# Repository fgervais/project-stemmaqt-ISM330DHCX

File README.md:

# ISM330DHCX Stemma QT Board

## Bus Pirate

### Read WHO_AM_I (Console)

```
HiZ> m
(1)> 4 (I2C)
(1)> 3 (~100KHz)

I2C> W
I2C> (1)
I2C> [0xd4 0x0f [0xd5 r]
I2C> w
```

## OSHPark

<a href="https://oshpark.com/shared_projects/3tg55XeU" target="_blank">https://oshpark.com/shared_projects/3tg55XeU</a>

## Related Projects

<a href="https://github.com/fgervais/project-nrf-princess-dress" target="_blank">https://github.com/fgervais/project-nrf-princess-dress</a>

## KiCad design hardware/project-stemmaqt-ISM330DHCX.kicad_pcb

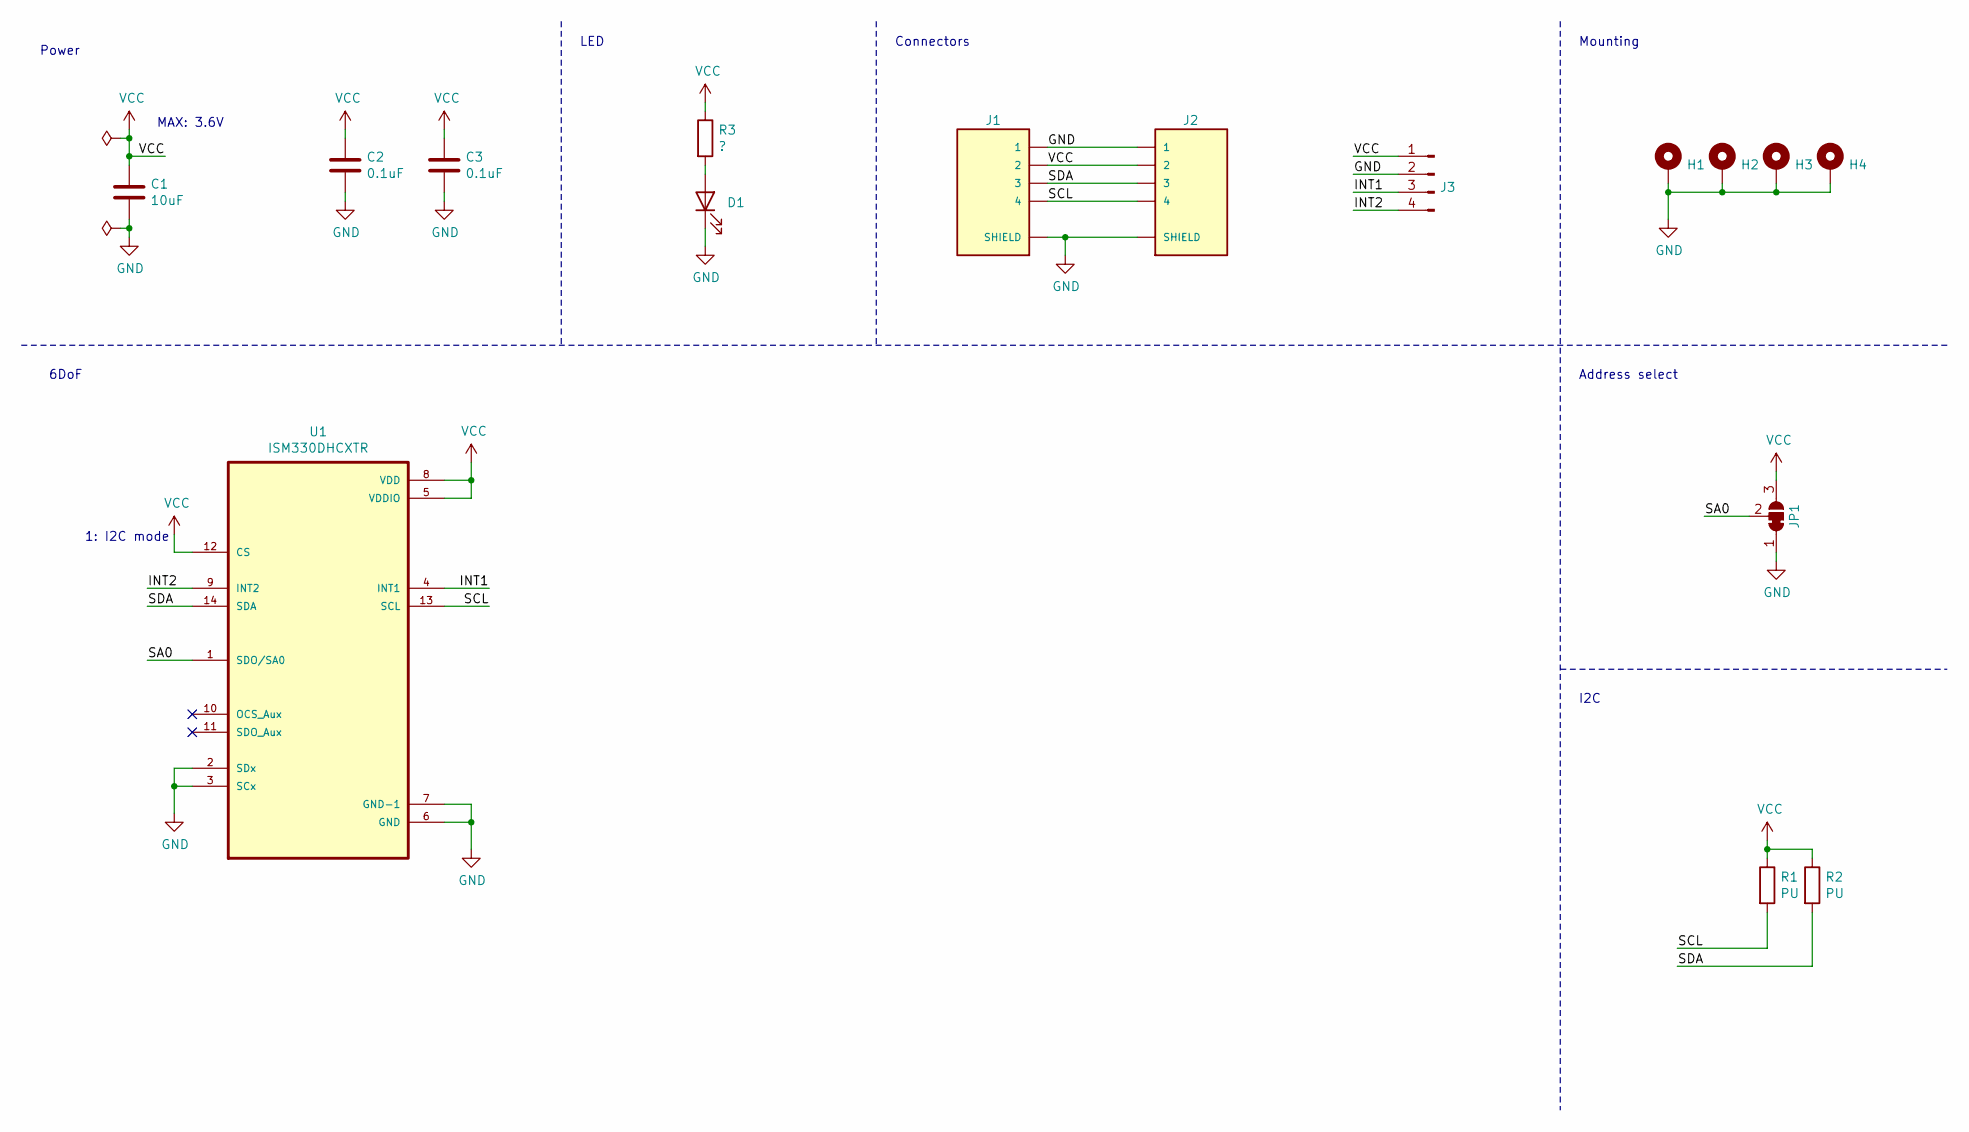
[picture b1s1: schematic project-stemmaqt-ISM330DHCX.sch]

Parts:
C1: 10uF; C_0805_2012Metric
C2, C3: 0.1uF; C_0603_1608Metric
D1: LED; LED_0603_1608Metric
H1, H2, H3, H4: MountingHole_Pad; MountingHole_2.2mm_M2_ISO7380_Pad
J1, J2: SM04B-SRSS-TB(LF)(SN); JST_SM04B-SRSS-TB(LF)(SN)
J3: Conn_01x04_Male; PinHeader_1x04_P2.54mm_Vertical
JP1: SolderJumper_3_Bridged12; SolderJumper-3_P1.3mm_Bridged12_RoundedPad1.0x1.5mm
R1, R2: PU; R_0603_1608Metric
R3: ?; R_0603_1608Metric
U1: ISM330DHCXTR; PQFN50P250X300X86-14N

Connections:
/INT1: J3.3, U1.4 (INT1)
/INT2: J3.4, U1.9 (INT2)
/SA0: JP1.2 (C), U1.1 (SDO/SA0)
/SCL: J1.4, J2.4, R1.2, U1.13 (SCL)
/SDA: J1.3, J2.3, R2.2, U1.14 (SDA)
GND: C1.2, C2.2, C3.2, D1.1 (K), H1.1, H2.1, H3.1, H4.1, J1.1, J1.S1 (SHIELD), J1.S2 (SHIELD), J2.1, J2.S1 (SHIELD), J2.S2 (SHIELD), J3.2, JP1.1 (A), U1.2 (SDx), U1.3 (SCx), U1.6 (GND), U1.7 (GND-1)
unnamed: D1.2 (A), R3.2
VCC: C1.1, C2.1, C3.1, J1.2, J2.2, J3.1, JP1.3 (B), R1.1, R2.1, R3.1, U1.5 (VDDIO), U1.8 (VDD), U1.12 (CS)

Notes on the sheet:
LED
Connectors
Mounting
6DoF
MAX: 3.6V
Power
1: I2C mode
Address select
I2C

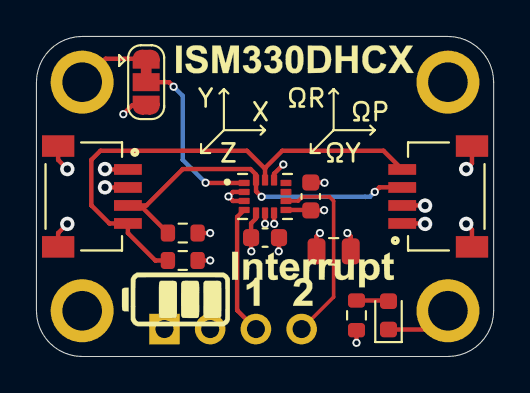
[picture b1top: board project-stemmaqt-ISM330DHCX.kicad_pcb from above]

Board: 4 copper layers, 25.4 x 17.8 mm, 20 parts (1 on the bottom side), 8 nets.

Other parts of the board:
Ref**: Val**; bunny-01
Ref**#2: Val**; ISM330DHCX
Ref**#3: Val**; ISM330DHCX Stemma interrupts
Ref**#4: Val**; Batería

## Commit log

2022-09-16 Start from project-stemmaqt-AS7341
2022-09-17 First draft
2022-09-20 Add the battery and interrupt graphics
2022-09-23 Add the board title graphic
2022-09-23 Add the bunny logo
2022-09-24 Add graphics
2022-09-24 Write my name correctly
2022-09-24 Refill planes
2022-11-30 Add the assembly plan
2022-12-03 Add the bus pirate test instructions
2022-12-03 Add the oshpark link
2022-12-09 Match first image white
2022-12-09 Move PCB image in the OSHPark section
